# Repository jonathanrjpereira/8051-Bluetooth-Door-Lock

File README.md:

# 8051 Bluetooth Door Lock

**Order PCB:** [PCBWay](https://www.pcbway.com/project/shareproject/Bluetooth_Door_Lock_using_8051.html)

The  main objective of this project is to unlock a garage door by an android application using a unique password entered through the android application device. Opening and closing & unlocking operation of garage door involves human labor. In this proposed system, the opening and closing & unlocking operation of a garage door is achieved by using an android application. The owner can connect an android application device to the system through Bluetooth, which in turn is connected through a HC-05 Bluetooth Module to a 8051 microcontroller controlled garage door that can open/close the door by entering the password. This method is very
convenient as one doesn’t have to get down of his car to open/close the door physically.
The user first has to pair a Smartphone with the HC-05 module; only then can the android application be used to transmit the password string to the HC-05 module. When the sent data (password entered by the user) matches with the password stored in the 8051 microcontroller, and then the 8051 microcontroller initiates a mechanism to open the door through a L293D motor driver interface.
In the case where the user does not have access to the Smartphone (battery low,  misplaced ,etc), a 4X4 keypad interface will acts as a secondary unlocking device. While entering the password through the 4X4 Keypad, an LCD display will provide visual feedback to the user. This will prevent the user from entering an incorrect password multiple times.
In cases where in the user enters an incorrect password repeatedly within a short period of time(3 incorrect tries per minute), the system automatically stops the acceptance of passwords from both the HC-05 Bluetooth module & the 4X4 keypad for a timeout period of 3 minutes. This will prevent hackers from brute forcing their way through the system. In such a case warning alarm or siren will be triggered by the 8051 microcontroller through a buzzer.
Unlike conventional IR consumer electronics, there is no IR code used to unlock the device because of the use of Bluetooth in the system. This makes it tougher to extract the password during communication & increases the security of the system.

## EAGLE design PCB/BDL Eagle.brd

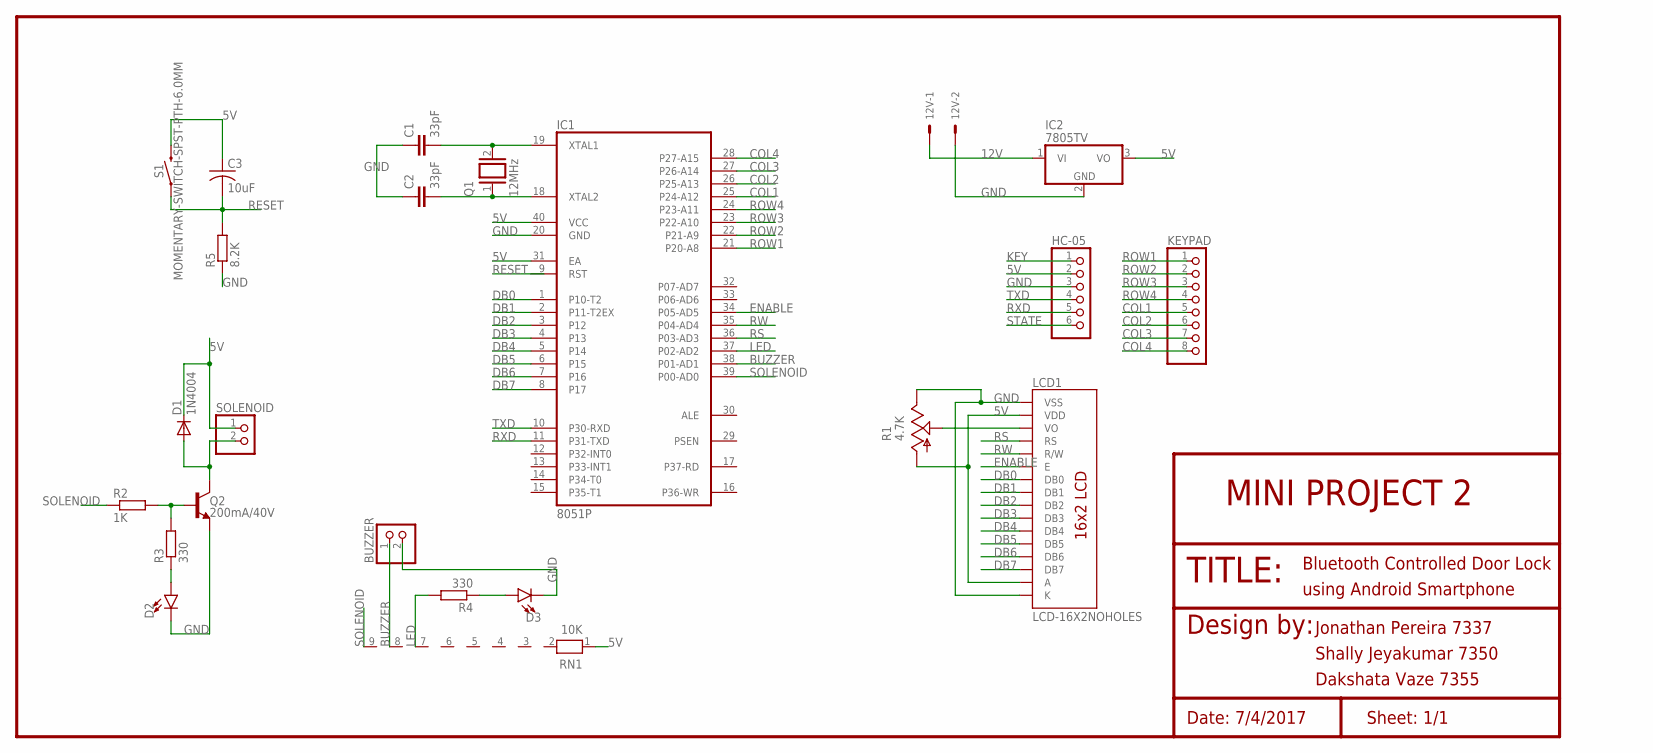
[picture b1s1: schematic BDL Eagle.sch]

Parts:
12V: KK-156-2
BUZZER: PINHD-1X2; 1X02
C1, C2: 33pF; C2.5-2
C3: 10uF; C025-050X050
D1: 1N4004; DO41-10
D2, D3: LED5MM; LED_5MM
HC-05: PINHD-1X6; 1X06
IC1: 8051P; DIL40
IC2: 7805TV; TO220V
KEYPAD: PINHD-1X8; 1X08
LCD1: LCD-16X2NOHOLES; LCD-16X2_NOHOLESNOSILK
Q1: 12MHz; QS
Q2: 200mA/40V; TO-92-EZ
R1: 4.7K; CA6V
R2: 1K; 0204/7
R3, R4: 330; 0204/7
R5: 8.2K; 0204/7
RN1: 10K; RN-9
S1: MOMENTARY-SWITCH-SPST-PTH-6.0MM; TACTILE_SWITCH_PTH_6.0MM
SOLENOID: PINHD-1X2; 1X02

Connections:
5V: C3.1, D1.C, HC-05.2, IC1.31 (EA), IC1.40 (VCC), IC2.3 (VO), LCD1.2 (VDD), LCD1.15 (A), R1.A, RN1.1, S1.3 (2), SOLENOID.1
12V: 12V.1, IC2.1 (VI)
BUZZER: BUZZER.1, IC1.38 (P01-AD1), RN1.8
COL1: IC1.25 (P24-A12), KEYPAD.5
COL2: IC1.26 (P25-A13), KEYPAD.6
COL3: IC1.27 (P26-A14), KEYPAD.7
COL4: IC1.28 (P27-A15), KEYPAD.8
DB0: IC1.1 (P10-T2), LCD1.7 (DB0)
DB1: IC1.2 (P11-T2EX), LCD1.8 (DB1)
DB2: IC1.3 (P12), LCD1.9 (DB2)
DB3: IC1.4 (P13), LCD1.10 (DB3)
DB4: IC1.5 (P14), LCD1.11 (DB4)
DB5: IC1.6 (P15), LCD1.12 (DB5)
DB6: IC1.7 (P16), LCD1.13 (DB6)
DB7: IC1.8 (P17), LCD1.14 (DB7)
ENABLE: IC1.34 (P05-AD5), LCD1.6 (E)
GND: 12V.2, BUZZER.2, C1.1, C2.1, D2.K (C), D3.K (C), HC-05.3, IC1.20 (GND), IC2.2 (GND), LCD1.1 (VSS), LCD1.16 (K), Q2.1 (E), R1.E, R5.1
KEY: HC-05.1
LED: IC1.37 (P02-AD2), R4.2, RN1.7
unnamed: C1.2, IC1.19 (XTAL1), Q1.2
unnamed: C2.2, IC1.18 (XTAL2), Q1.1
unnamed: D2.A, R3.1
unnamed: Q2.2 (B), R2.2, R3.2
unnamed: D3.A, R4.1
unnamed: D1.A, Q2.3 (C), SOLENOID.2
RESET: C3.2, R5.2, S1.1
ROW1: IC1.21 (P20-A8), KEYPAD.1
ROW2: IC1.22 (P21-A9), KEYPAD.2
ROW3: IC1.23 (P22-A10), KEYPAD.3
ROW4: IC1.24 (P23-A11), KEYPAD.4
RS: IC1.36 (P03-AD3), LCD1.4 (RS)
RW: IC1.35 (P04-AD4), LCD1.5 (R/W)
RXD: HC-05.5, IC1.11 (P31-TXD)
SOLENOID: IC1.39 (P00-AD0), R2.1, RN1.9
STATE: HC-05.6
TXD: HC-05.4, IC1.10 (P30-RXD)
VO: LCD1.3 (VO), R1.S

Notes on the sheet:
TITLE:
Bluetooth Controlled Door Lock
using Android Smartphone
Design by:
Jonathan Pereira 7337
Shally Jeyakumar 7350
Dakshata Vaze 7355
Date: 7/4/2017
Sheet: 1/1
MINI PROJECT 2

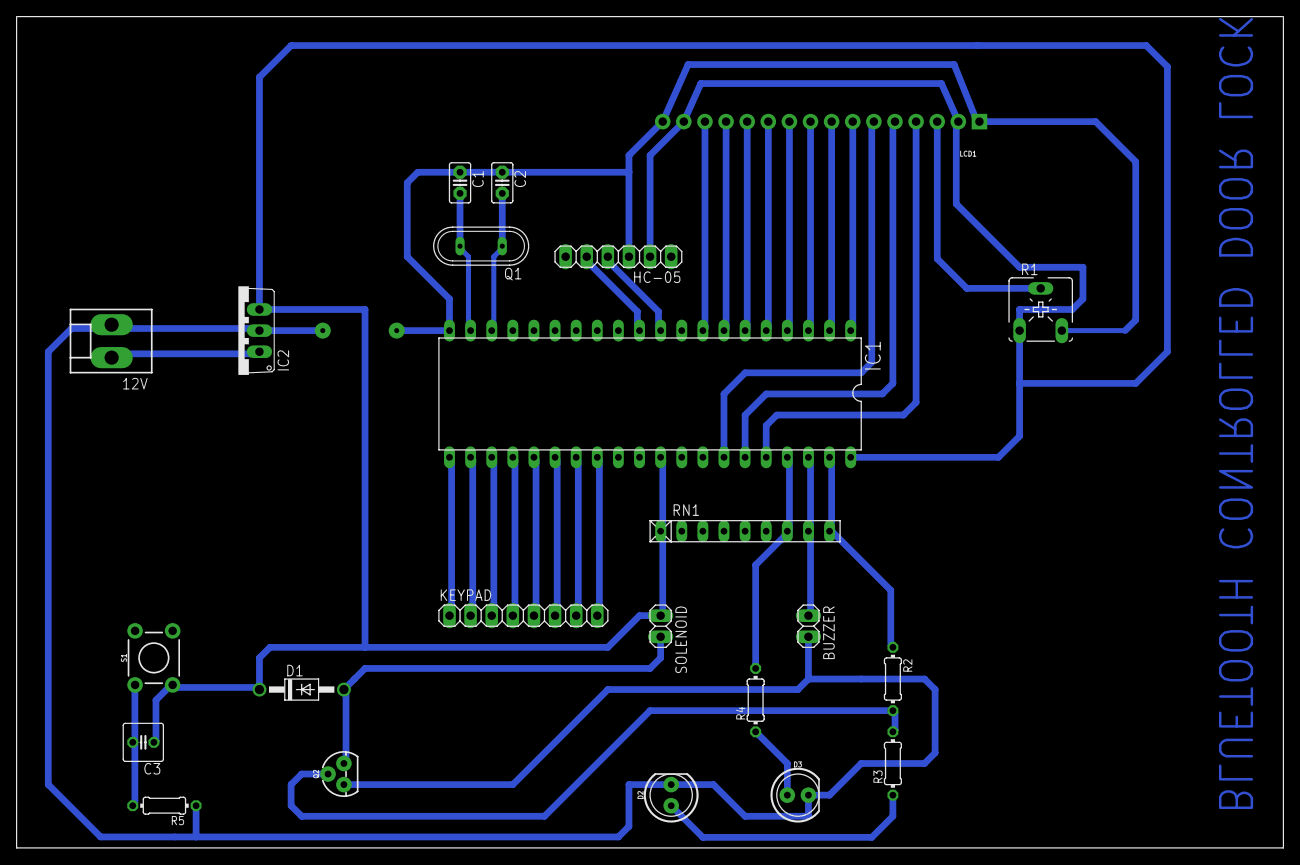
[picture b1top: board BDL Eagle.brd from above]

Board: 2 copper layers, 152.4 x 100.0 mm, 23 parts (0 on the bottom side), 35 nets.

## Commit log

2017-08-03 Code, PCB Files & Documentation
2017-08-03 Project Image
2017-11-06 Schematic and Board View

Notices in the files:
parts and their libraries:
SparkFun-Displays: Licensing: Creative Commons ShareAlike 4.0 International - https://creativecommons.org/licenses/by-sa/4.0
